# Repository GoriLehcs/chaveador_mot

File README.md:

# MOT Anti-Helmholtz Coil Switcher

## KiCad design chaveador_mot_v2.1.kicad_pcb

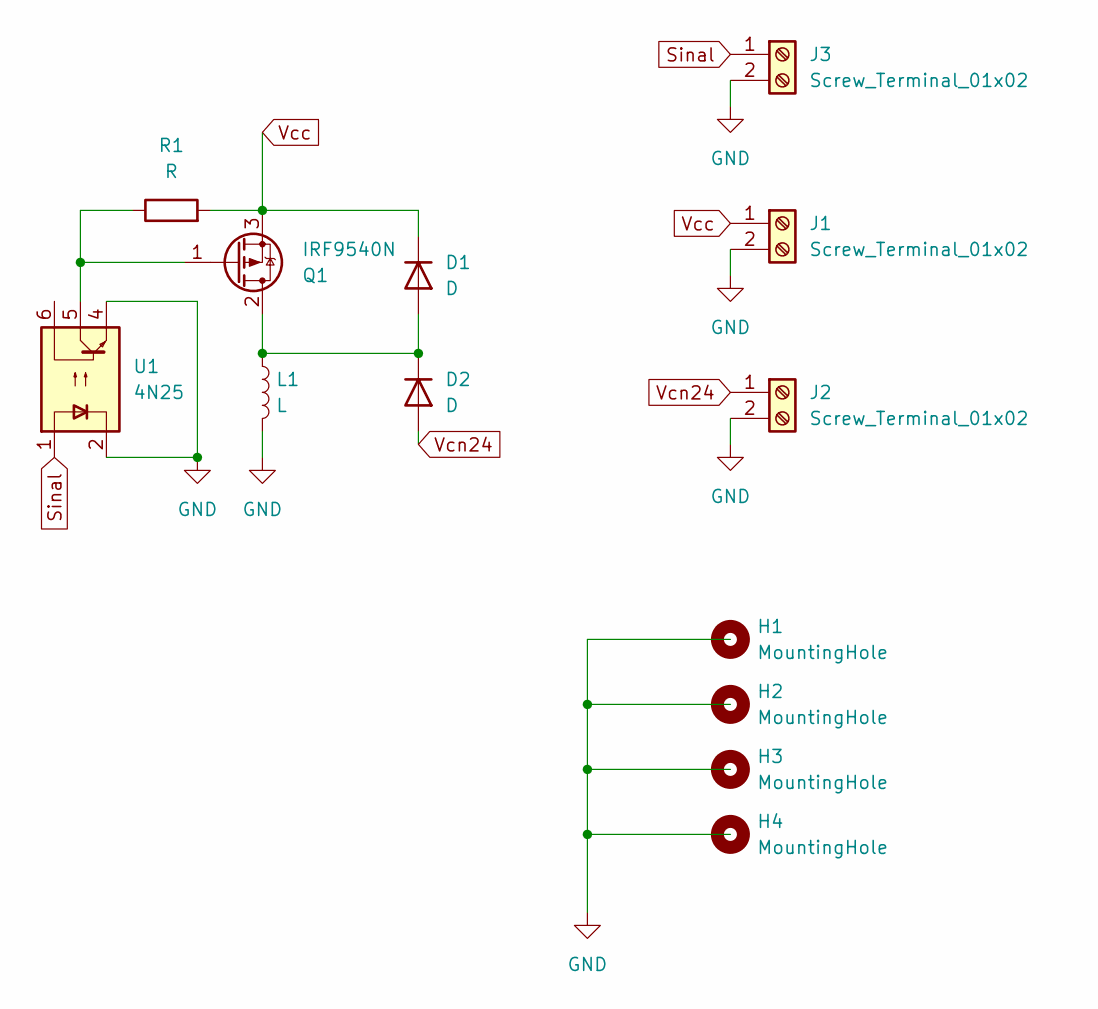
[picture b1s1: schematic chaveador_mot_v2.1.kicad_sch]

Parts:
D1, D2: D; D_A-405_P10.16mm_Horizontal
H1, H2, H3, H4: MountingHole; MountingHole_2.5mm_Pad
J1, J2, J3: Screw_Terminal_01x02; TerminalBlock_Phoenix_MKDS-1,5-2_1x02_P5.00mm_Horizontal
L1: L; TerminalBlock_Phoenix_MKDS-1,5-2_1x02_P5.00mm_Horizontal
Q1: IRF9540N; TO-220-3_Vertical
R1: R; R_Axial_DIN0207_L6.3mm_D2.5mm_P10.16mm_Horizontal
U1: 4N25; DIP-6_W7.62mm

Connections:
GND: J1.2, J2.2, J3.2, L1.2, U1.2, U1.4
unnamed: D1.2 (A), D2.1 (K), L1.1, Q1.2 (D)
unnamed: Q1.1 (G), R1.1, U1.5
Sinal: J3.1, U1.1
Vcc: D1.1 (K), J1.1, Q1.3 (S), R1.2
Vcn24: D2.2 (A), J2.1

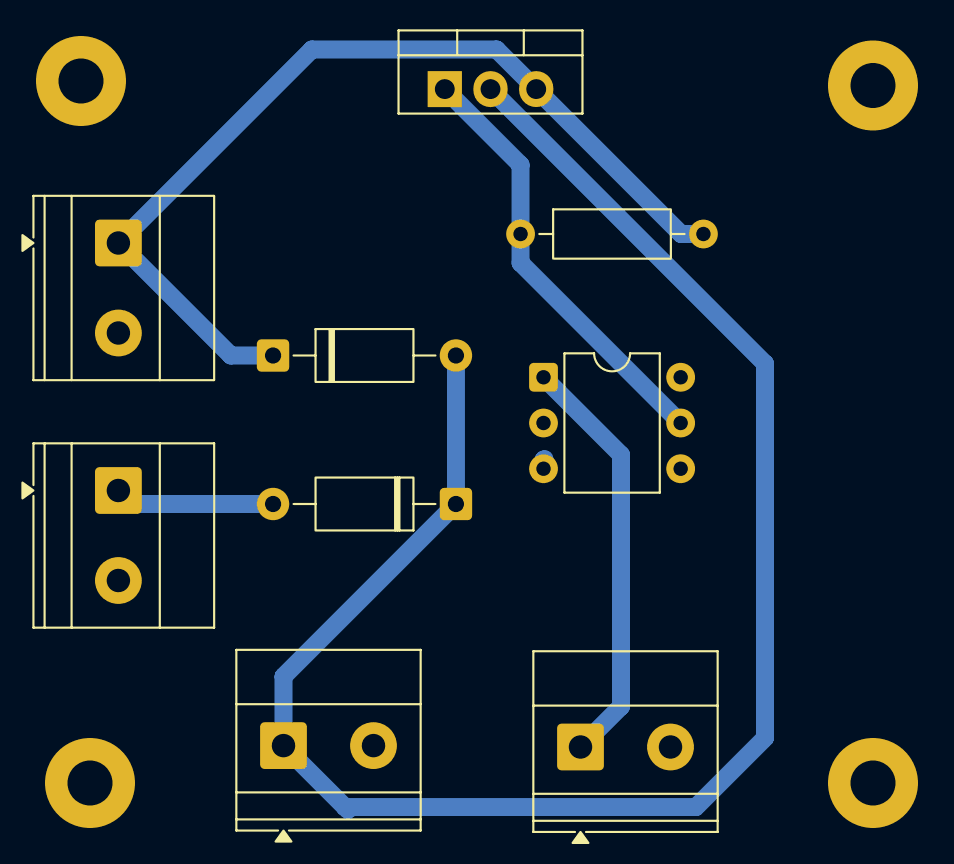
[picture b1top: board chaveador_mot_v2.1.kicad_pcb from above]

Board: 2 copper layers, 13 parts (0 on the bottom side), 6 nets.
